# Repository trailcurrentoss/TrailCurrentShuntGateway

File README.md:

# TrailCurrent Shunt Gateway

Gateway module that reads battery monitoring data from a Victron BMV battery shunt via serial and transmits the readings over a CAN bus interface. Part of the [TrailCurrent](https://trailcurrent.com) open-source vehicle platform.

## Hardware Overview

- **Microcontroller:** ESP32
- **Function:** Serial-to-CAN bus bridge for Victron BMV battery shunt data
- **Key Features:**
  - Victron BMV VE.Direct serial protocol parsing
  - CAN bus output at 500 kbps
  - Battery voltage, current, SOC, and wattage reporting
  - Hierarchical PCB schematic design with FreeCAD enclosure
  - 8 LED status indicators

## Hardware Requirements

### Components

- **Microcontroller:** ESP32 development board
- **CAN Transceiver:** Vehicle CAN bus interface (TX: GPIO 15, RX: GPIO 13)
- **Serial Input:** Victron BMV VE.Direct connection (Serial2: TX GPIO 17, RX GPIO 16 at 19200 baud)
- **LED Indicators:** 8 status LEDs (GPIOs 32, 33, 26, 14, 23, 19, 17, 4)

### KiCAD Library Dependencies

This project uses the consolidated [TrailCurrentKiCADLibraries](https://github.com/trailcurrentoss/TrailCurrentKiCADLibraries).

**Setup:**

```bash
# Clone the library
git clone git@github.com:trailcurrentoss/TrailCurrentKiCADLibraries.git

# Set environment variables (add to ~/.bashrc or ~/.zshrc)
export TRAILCURRENT_SYMBOL_DIR="/path/to/TrailCurrentKiCADLibraries/symbols"
export TRAILCURRENT_FOOTPRINT_DIR="/path/to/TrailCurrentKiCADLibraries/footprints"
export TRAILCURRENT_3DMODEL_DIR="/path/to/TrailCurrentKiCADLibraries/3d_models"
```

See [KICAD_ENVIRONMENT_SETUP.md](https://github.com/trailcurrentoss/TrailCurrentKiCADLibraries/blob/main/KICAD_ENVIRONMENT_SETUP.md) in the library repository for detailed setup instructions.

## Opening the Project

1. **Set up environment variables** (see Library Dependencies above)
2. **Open KiCAD:**
   ```bash
   kicad EDA/trailer-shunt-can-bus.kicad_pro
   ```
3. **Verify libraries load** - All symbol and footprint libraries should resolve without errors
4. **View 3D models** - Open PCB and press `Alt+3` to view the 3D visualization

### Schematic Sheets

The design uses a hierarchical schematic with dedicated sheets:
- **Root** - Top-level connections
- **Power** - Power distribution and regulation
- **CAN** - CAN bus transceiver interface
- **MCU** - ESP32 microcontroller and support circuits
- **Connectivity** - Serial interface to Victron BMV

## Firmware

See `src/` directory for PlatformIO-based firmware.

**Setup:**
```bash
# Install PlatformIO (if not already installed)
pip install platformio

# Build firmware
pio run

# Upload to board
pio run -t upload
```

### Victron BMV Parameters

The firmware parses the following VE.Direct protocol fields:

| Parameter | Description |
|-----------|-------------|
| V | Battery voltage |
| I | Battery current (with sign) |
| P | Power/wattage (with sign) |
| SOC | State of charge |
| TTG | Time to go |
| CE | Consumed energy |
| H1-H12, H17-H18 | Historical data |

### CAN Bus Protocol

The gateway transmits two messages at 500 kbps with a 33ms update cycle:

**Message 0x23** (7 bytes) - Battery basics:

| Byte | Description |
|------|-------------|
| 0 | Battery voltage (whole) |
| 1 | Battery voltage (decimal) |
| 2 | Current sign |
| 3 | Current (whole) |
| 4 | Current (decimal) |
| 5 | SOC (whole) |
| 6 | SOC (decimal) |

**Message 0x24** (5 bytes) - Power metrics:

| Byte | Description |
|------|-------------|
| 0 | Wattage sign |
| 1 | Wattage MSB |
| 2 | Wattage LSB |
| 3 | TTG MSB |
| 4 | TTG LSB |

## Manufacturing

- **PCB Files:** Ready for fabrication via standard PCB services (JLCPCB, OSH Park, etc.)
- **BOM Generation:** Export BOM from KiCAD schematic (Tools > Generate BOM)
- **Enclosure:** FreeCAD design included in `CAD/` directory
- **JLCPCB Assembly:** See [BOM_ASSEMBLY_WORKFLOW.md](https://github.com/trailcurrentoss/TrailCurrentKiCADLibraries/blob/main/BOM_ASSEMBLY_WORKFLOW.md) for detailed assembly workflow

## Project Structure

```
├── CAD/                          # FreeCAD enclosure design
├── EDA/                          # KiCAD hardware design files
│   ├── trailer-shunt-can-bus.kicad_pro
│   ├── trailer-shunt-can-bus.kicad_sch  # Root schematic
│   ├── can.kicad_sch             # CAN subsystem
│   ├── connectivity.kicad_sch    # Serial interface
│   ├── mcu.kicad_sch             # MCU subsystem
│   ├── power.kicad_sch           # Power subsystem
│   └── trailer-shunt-can-bus.kicad_pcb  # PCB layout
├── src/                          # Firmware source
│   ├── main.cpp                  # Victron BMV parser and CAN transmitter
│   ├── globals.h                 # Pin definitions and debug macros
│   └── canHelper.h               # CAN bus configuration
└── platformio.ini                # Build configuration
```

## License

MIT License - See LICENSE file for details.

This is open source hardware. You are free to use, modify, and distribute these designs under the terms of the MIT license.

## Contributing

Improvements and contributions are welcome! Please submit issues or pull requests.

## Support

For questions about:
- **KiCAD setup:** See [KICAD_ENVIRONMENT_SETUP.md](https://github.com/trailcurrentoss/TrailCurrentKiCADLibraries/blob/main/KICAD_ENVIRONMENT_SETUP.md)
- **Assembly workflow:** See [BOM_ASSEMBLY_WORKFLOW.md](https://github.com/trailcurrentoss/TrailCurrentKiCADLibraries/blob/main/BOM_ASSEMBLY_WORKFLOW.md)

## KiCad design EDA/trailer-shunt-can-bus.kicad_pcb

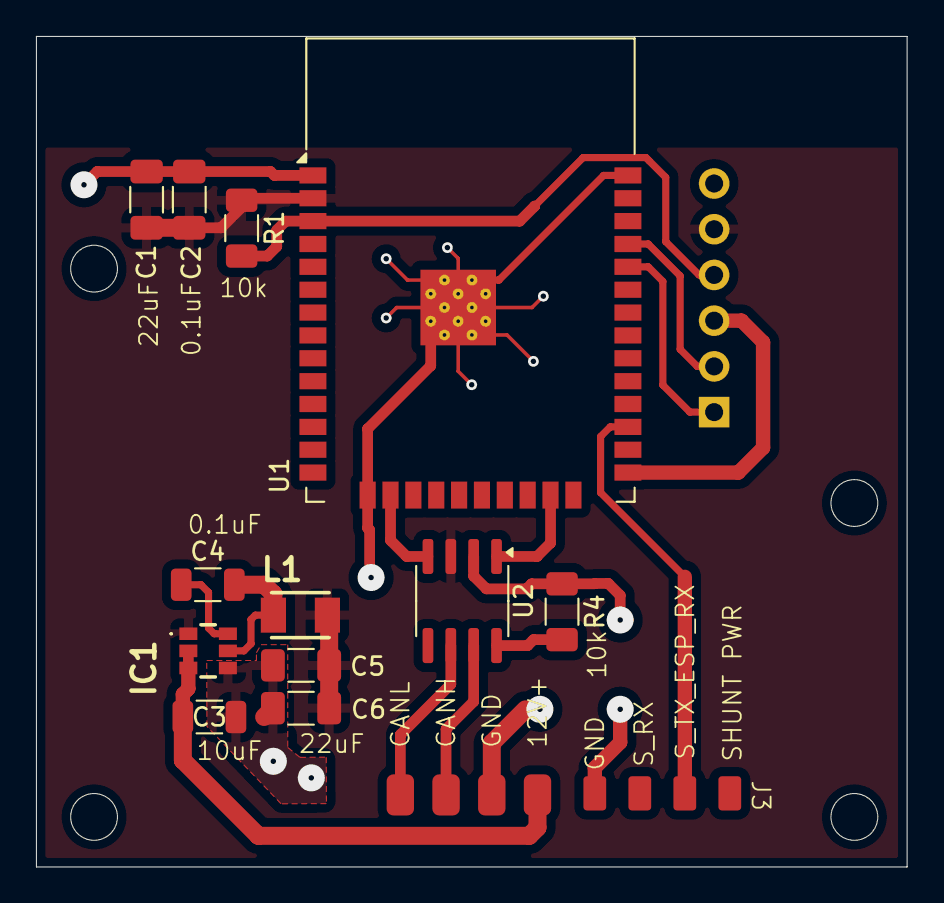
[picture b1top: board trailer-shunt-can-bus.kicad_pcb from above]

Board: 2 copper layers, 48.4 x 46.1 mm, 15 parts (1 on the bottom side), 15 nets.

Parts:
C1, C5, C6: 22uF; C_1206_3216Metric_Pad1.33x1.80mm_HandSolder
C2: 0.1uF; C_1206_3216Metric_Pad1.33x1.80mm_HandSolder
C3: 10uF; C_1206_3216Metric
C4: 100nF; C_1206_3216Metric
IC1: AP63203WU-7; AP63203WU7
J1: Conn_01x06; PinHeader_1x06_P2.54mm_Horizontal
J2: Conn_01x04; CAN_PLUS_POWER
J3: Conn_01x04; GenericPad_01x04
L1: NLV32T-3R9J-EF (3.9uH); NLV32T-3R9J-EF
R1, R4: 10k; R_1206_3216Metric_Pad1.30x1.75mm_HandSolder
U1: ESP32-WROOM-32
U2: SN65HVD230; SOIC-8_3.9x4.9mm_P1.27mm

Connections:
+3.3V: C1.1, C2.1, C5.1, C6.1, IC1.1 (FB), J1.5, L1.2, R1.1, U1.2 (VDD), U2.3 (VCC)
+12V: C3.1, IC1.2 (EN), IC1.3 (VIN), J2.1
CANH: J2.3, U2.7 (CANH)
CANL: J2.4, U2.6 (CANL)
CAN_RX: U1.16 (IO13), U2.4 (R)
CAN_TX: U1.23 (IO15), U2.1 (D)
EN: J1.4, R1.2, U1.3 (EN)
ESP32_RX: J1.1, U1.34 (RXD0/IO3)
ESP32_TX: J1.2, U1.35 (TXD0/IO1)
GND: C1.2, C2.2, C3.2, C5.2, C6.2, IC1.4 (GND), J1.6, J2.2, J3.1, R4.1, U1.1 (GND), U1.15 (GND), U1.38 (GND), U1.39 (GND), U2.2 (GND)
IO0: J1.3, U1.25 (IO0)
unnamed: C4.1, IC1.6 (BST)
unnamed: C4.2, IC1.5 (SW), L1.1
unnamed: R4.2, U2.8 (Rs)
SHUNT_DATA: J3.3, U1.27 (IO16)

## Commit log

2026-02-12 Starting project
2026-02-14 Fixing license
2026-02-14 Update docs: replace Codeberg URLs with GitHub references
2026-02-22 Updated housing to have logo
2026-02-23 Add trailcurrent.com link to README
